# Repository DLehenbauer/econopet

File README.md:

# EconoPET

Open hardware mainboard replacement for Commodore PET/CBM 2001/30xx/40xx/80xx machines. The EconoPET can also run standalone with HDMI display and USB keyboard.

## User Resources

See the [project page](https://dlehenbauer.github.io/econopet) for user manual and firmware updates.

## Manufacturing

> **⚠️ Warning:** Rev A is not perfect. Before ordering, review the currently [known issues](https://github.com/DLehenbauer/econopet/issues?q=is%3Aissue%20label%3Arev-a%20label%3Aerrata) and understand that new issues may be discovered over time.

Rev. A has been released. For manufacturing and assembly instructions, go [here](https://dlehenbauer.github.io/econopet/manual/build-an-econopet/).

## Development

This project uses a [Dev Container](https://containers.dev/) for a consistent development environment on Windows, macOS, and Linux.

### Prerequisites

- [Docker](https://www.docker.com/)
- [VS Code](https://code.visualstudio.com/)
- [Dev Containers extension](https://marketplace.visualstudio.com/items?itemName=ms-vscode-remote.remote-containers)

### Workflow

This project uses [CMake](https://cmake.org/) to manage the build process for firmware, gateware, ROMs, and SD card package.

```sh
# Configure
cmake --preset default              # Do this first

# Build
cmake --build --preset all          # Build everything
cmake --build --preset boot         # Build the EconoPET SD-card bootloader
cmake --build --preset fw           # Build firmware only
cmake --build --preset fw-test      # Build firmware tests only
cmake --build --preset sys-test     # Build system integration tests
cmake --build --preset gw           # Build gateware only
cmake --build --preset rom          # Build ROMs only
cmake --build --preset sdcard       # Build SD card package

# Build and Program
cmake --build --preset prog-boot    # Build and program bootloader (over SWD)
cmake --build --preset prog-fw      # Build and program firmware (over SWD)
cmake --build --preset prog-gw      # Build and program gateware (over SWD)
cmake --build --preset prog         # Build and program bootloader, gateware, and firmware (over SWD)
cmake --build --preset reset        # Reset the MCU without reprogramming (over SWD)

# Test
ctest --preset all --parallel       # Run all tests
ctest --preset fw --parallel        # Run firmware tests only
ctest --preset sys                  # Run system integration suite only
ctest --preset gw --parallel        # Run gateware unit tests only
ctest --preset gw-boot --parallel   # Run full-boot benches (Verilator, minutes)
```

Gateware benches run under both simulators. `gw` runs both quick suites;
`gw-iv` and `gw-vl` run only Icarus or Verilator, respectively. Verilator is
two-state and settles differently, so it catches races Icarus tolerates. Each
suite takes under a minute. `ECONOPET_MEDIA_DIR` must point at the directory
containing `roms/` and `disks/`; `top_tb` and the boot bench load real ROMs
from its `roms/` subdirectory.

The [integration-test author guide](test/system/README.md) covers host, board
and firmware fixtures, checked CPU programs, ROM calls, and cooperative phases.
Use its nested CTest commands to filter individual integration cases or set
inner parallelism. The root `sys` preset selects the aggregate wrapper.

`gw-boot` is separate because it simulates seconds of PET time: it boots the
stock BASIC-4 ROMs on the soft 6502 and passes only once the banner, the RAM
sizing result and the `READY.` prompt are all on screen. That takes ~5 minutes
under Verilator and is impractical under Icarus. It prints the screen at the
end and writes `gw/EconoPET/outflow/stock6502_boot_tb.pgm`:

```
|*** COMMODORE BASIC 4.0 ***             |
|                                        |
| 31743 BYTES FREE                       |
|                                        |
|READY.                                  |
```

`ctest` hides that on success, so use `ctest --preset gw-boot --parallel -V` to see it, or
run `./verilate.sh stock6502_boot_tb 0` directly. See
[docs/dev/verilator.md](docs/dev/verilator.md) for the Verilator runner and
[docs/dev/testing.md](docs/dev/testing.md) for test seeding and replay.

## License

This project is released under the [CC0 1.0 Universal](LICENSE) (CC0) license, placing it in the public domain.

**Exception:** external dependencies are subject to their own licenses as noted in their respective source code and in [NOTICE.md](NOTICE.md).

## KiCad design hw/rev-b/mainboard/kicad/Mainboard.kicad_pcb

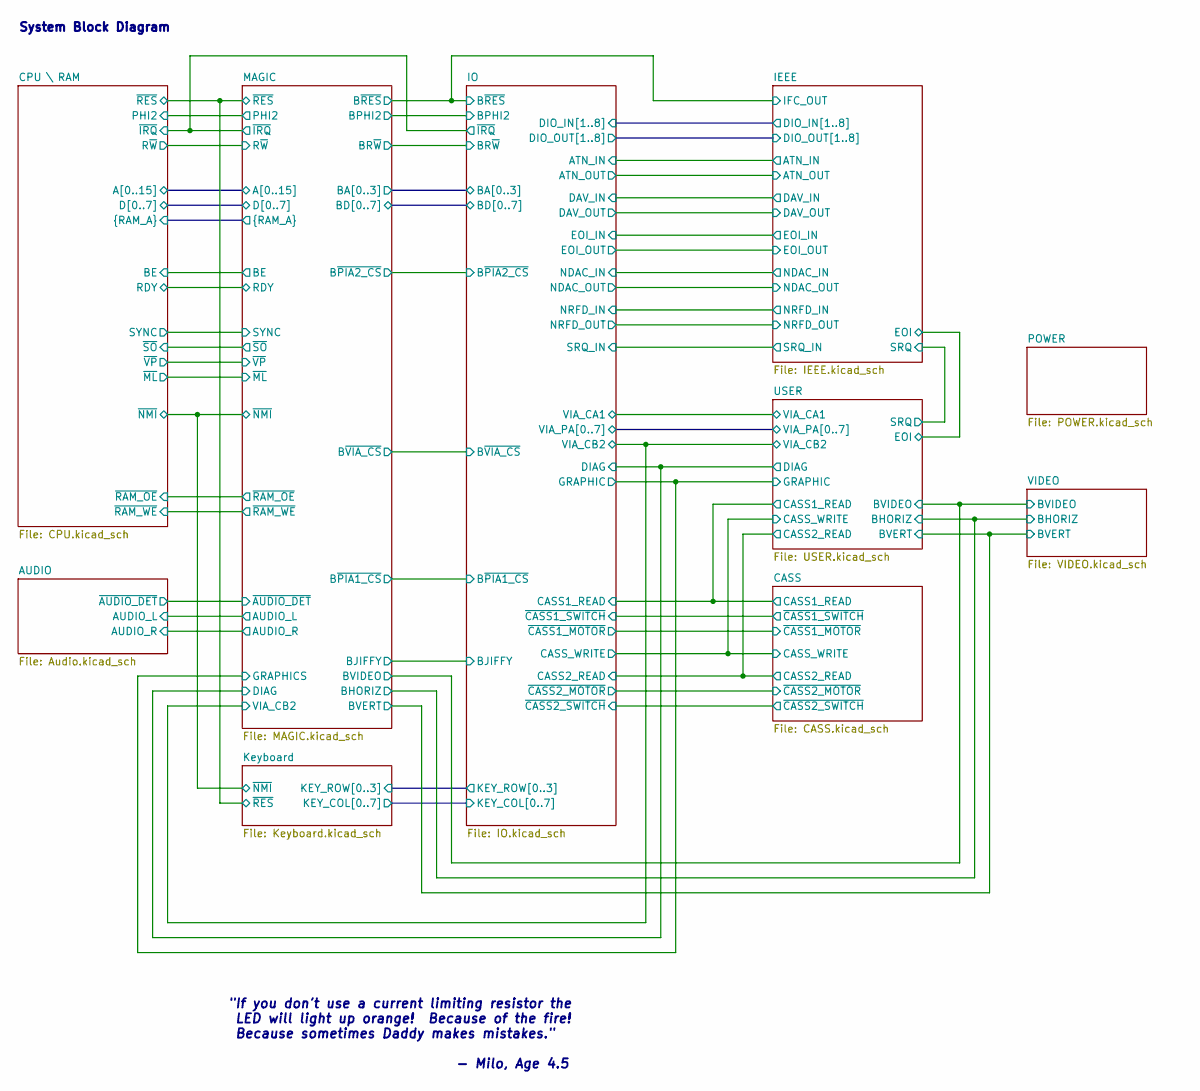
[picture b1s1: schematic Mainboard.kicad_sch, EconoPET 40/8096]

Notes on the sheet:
"If you don't use a current limiting resistor the LED will light up orange! Because of the fire! Because sometimes Daddy makes mistakes." - Milo, Age 4.5
System Block Diagram

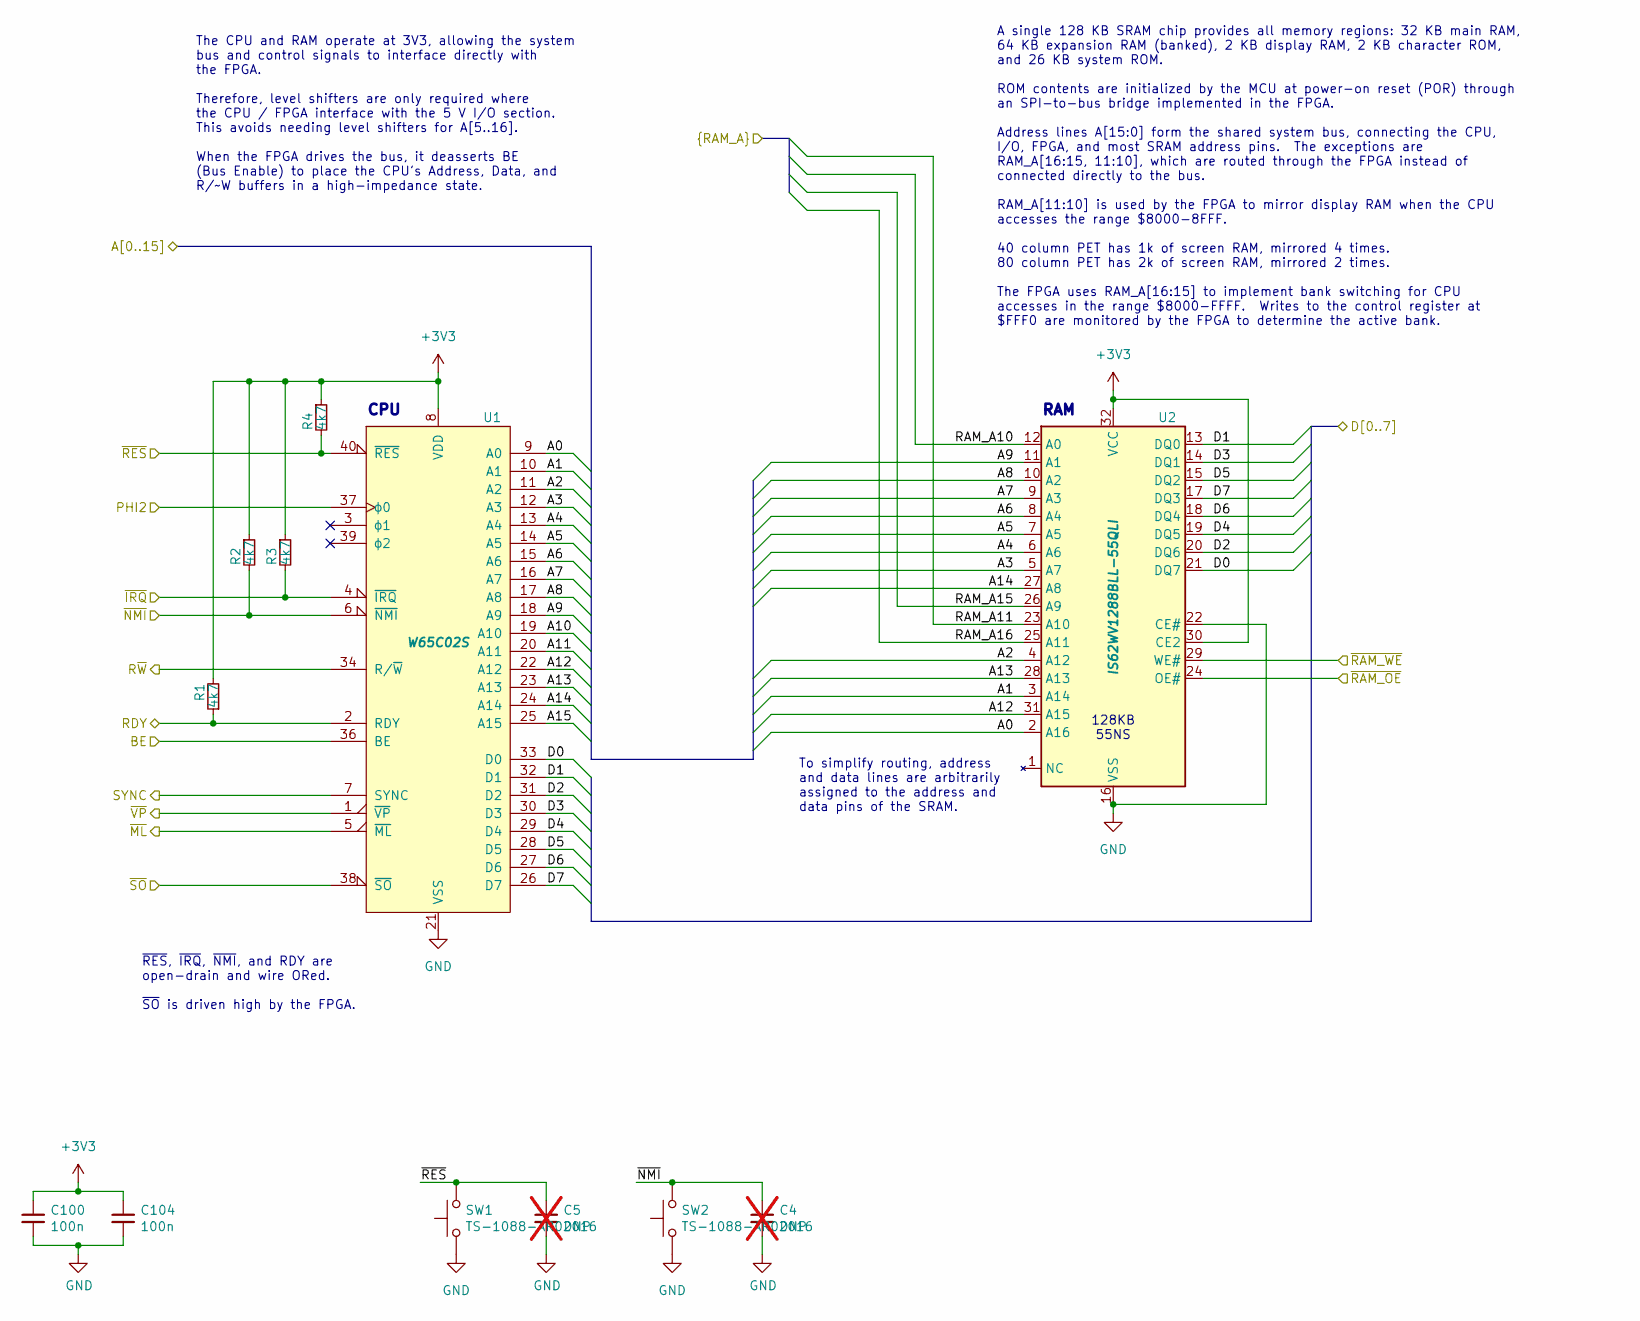
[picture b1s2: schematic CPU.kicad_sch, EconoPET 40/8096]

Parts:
C4, C5: DNP; C_0402_1005Metric; not fitted
C100, C104: 100n; C_0402_1005Metric; LCSC Part # C307331
R1, R2, R3, R4: 4k7; R_0402_1005Metric; LCSC Part # C25900
SW1, SW2: TS-1088-AR02016; SW-SMD_L3.9-W3.0-P4.45; LCSC Part # C720477
U1: W65C02S; DIP-40_W15.24mm_Socket; MOUSER 955-W65C02S6TPG-14,571-1-2199299-5
U2: IS62WV1288BLL-55QLI; SOP-32_L20.7-W11.3-P1.27-LS14.1-BL; LCSC Part # C1351025

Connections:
+3V3: C100.1, C104.1, R1.2, R2.1, R3.1, R4.1, U1.8 (VDD), U2.30 (CE2), U2.32 (VCC); also elsewhere on the board
/CPU \ RAM/A0: U1.9 (A0), U2.2 (A16); also elsewhere on the board
/CPU \ RAM/A1: U1.10 (A1), U2.3 (A14); also elsewhere on the board
/CPU \ RAM/A2: U1.11 (A2), U2.4 (A12); also elsewhere on the board
/CPU \ RAM/A3: U1.12 (A3), U2.5 (A7); also elsewhere on the board
/CPU \ RAM/A4: U1.13 (A4), U2.6 (A6); also elsewhere on the board
/CPU \ RAM/A5: U1.14 (A5), U2.7 (A5); also elsewhere on the board
/CPU \ RAM/A6: U1.15 (A6), U2.8 (A4); also elsewhere on the board
/CPU \ RAM/A7: U1.16 (A7), U2.9 (A3); also elsewhere on the board
/CPU \ RAM/A8: U1.17 (A8), U2.10 (A2); also elsewhere on the board
/CPU \ RAM/A9: U1.18 (A9), U2.11 (A1); also elsewhere on the board
/CPU \ RAM/A10: U1.19 (A10); also elsewhere on the board
/CPU \ RAM/A11: U1.20 (A11); also elsewhere on the board
/CPU \ RAM/A12: U1.22 (A12), U2.31 (A15); also elsewhere on the board
/CPU \ RAM/A13: U1.23 (A13), U2.28 (A13); also elsewhere on the board
/CPU \ RAM/A14: U1.24 (A14), U2.27 (A8); also elsewhere on the board
/CPU \ RAM/A15: U1.25 (A15); also elsewhere on the board
/CPU \ RAM/D0: U1.33 (D0), U2.21 (DQ7); also elsewhere on the board
/CPU \ RAM/D1: U1.32 (D1), U2.13 (DQ0); also elsewhere on the board
/CPU \ RAM/D2: U1.31 (D2), U2.20 (DQ6); also elsewhere on the board
/CPU \ RAM/D3: U1.30 (D3), U2.14 (DQ1); also elsewhere on the board
/CPU \ RAM/D4: U1.29 (D4), U2.19 (DQ5); also elsewhere on the board
/CPU \ RAM/D5: U1.28 (D5), U2.15 (DQ2); also elsewhere on the board
/CPU \ RAM/D6: U1.27 (D6), U2.18 (DQ4); also elsewhere on the board
/CPU \ RAM/D7: U1.26 (D7), U2.17 (DQ3); also elsewhere on the board
/CPU \ RAM/RAM_A10: U2.12 (A0); also elsewhere on the board
/CPU \ RAM/RAM_A11: U2.23 (A10); also elsewhere on the board
/CPU \ RAM/RAM_A15: U2.26 (A9); also elsewhere on the board
/CPU \ RAM/RAM_A16: U2.25 (A11); also elsewhere on the board
/CPU \ RAM/~ML: U1.5 (~ML); also elsewhere on the board
/CPU \ RAM/~NMI: C4.1, R2.2, SW2.2, U1.6 (~NMI); also elsewhere on the board
/CPU \ RAM/~RAM_OE: U2.24 (OE#); also elsewhere on the board
/CPU \ RAM/~RAM_WE: U2.29 (WE#); also elsewhere on the board
/CPU \ RAM/~RES: C5.1, R4.2, SW1.2, U1.40 (~RES); also elsewhere on the board
/CPU \ RAM/~VP: U1.1 (~VP); also elsewhere on the board
/MAGIC/FPGA/BE: U1.36 (BE); also elsewhere on the board
/MAGIC/FPGA/RDY: R1.1, U1.2 (RDY); also elsewhere on the board
/MAGIC/FPGA/SYNC: U1.7 (SYNC); also elsewhere on the board
/MAGIC/FPGA/~IRQ: R3.2, U1.4 (~IRQ); also elsewhere on the board
/MAGIC/FPGA/~SO: U1.38 (~SO); also elsewhere on the board
/MAGIC/PHI2: U1.37 (ϕ0); also elsewhere on the board
/MAGIC/R~W: U1.34 (R/~W); also elsewhere on the board
GND: C4.2, C5.2, C100.2, C104.2, SW1.1, SW2.1, U1.21 (VSS), U2.16 (VSS), U2.22 (CE#); also elsewhere on the board

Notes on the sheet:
RAM
A single 128 KB SRAM chip provides all memory regions: 32 KB main RAM, 64 KB expansion RAM (banked), 2 KB display RAM, 2 KB character ROM, and 26 KB system ROM. ROM contents are initialized by the MCU at power-on reset (POR) through an SPI-to-bus bridge implemented in the FPGA. Address lines A[15:0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
To simplify routing, address and data lines are arbitrarily assigned to the address and data pins of the SRAM.
~{RES}, ~{IRQ}, ~{NMI}, and RDY are open-drain and wire ORed. ~{SO} is driven high by the FPGA.
128KB 55NS
CPU
The CPU and RAM operate at 3V3, allowing the system bus and control signals to interface directly with the FPGA. Therefore, level shifters are only required where the CPU / FPGA interface with the 5 V I/O section. This avoids needing level shifters for A[5..16]. When the FPGA drives the bus, it dea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

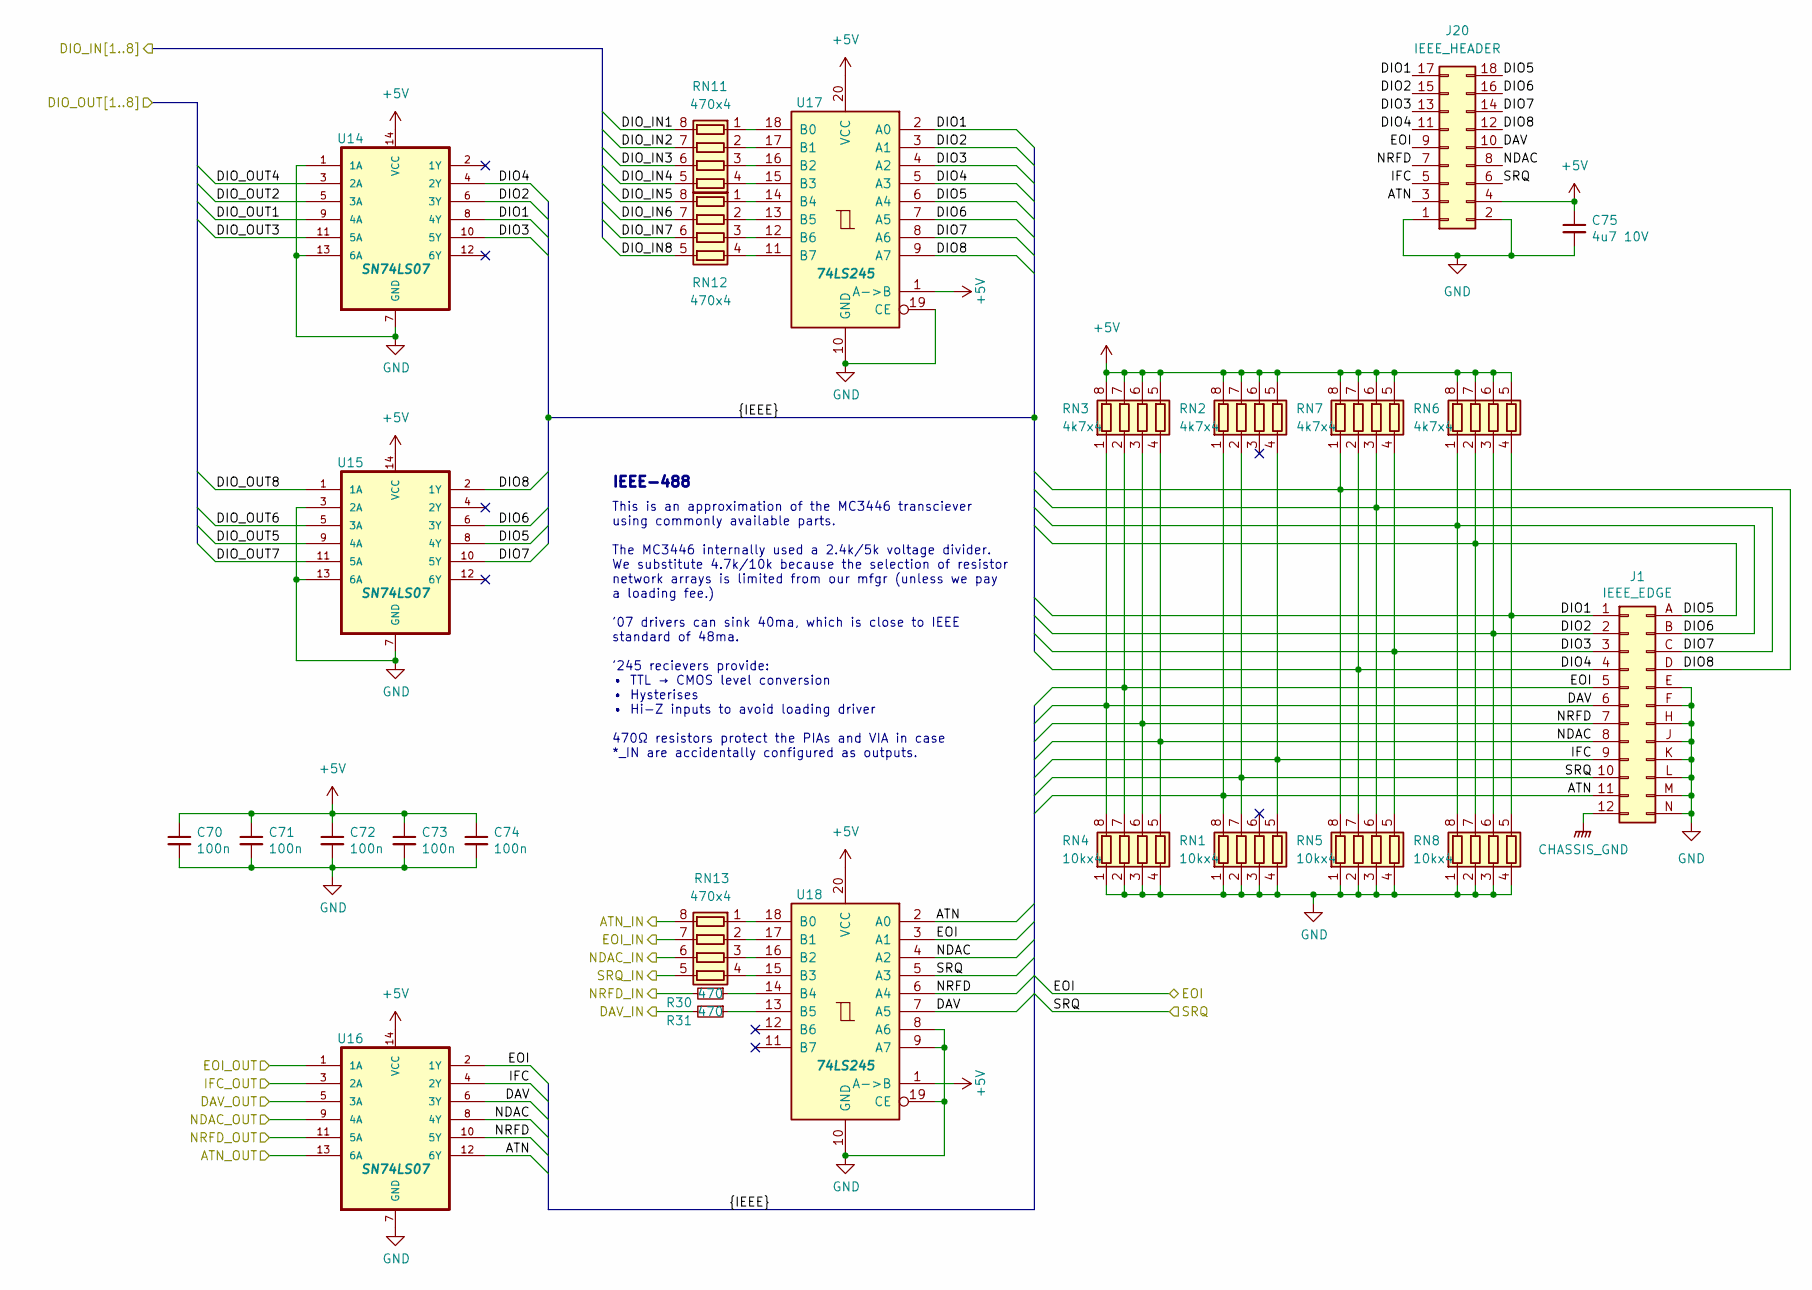
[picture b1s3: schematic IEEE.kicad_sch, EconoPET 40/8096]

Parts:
C70, C71, C72, C73, C74: 100n; C_0402_1005Metric; LCSC Part # C307331
C75: 4u7 10V; C_0402_1005Metric; LCSC Part # C23733
J1: IEEE_EDGE; CBM_PET_IEEE_EDGE_CON_24P
J20: IEEE_HEADER; PinHeader_2x09_P2.54mm_Vertical; MOUSER 649-1012938195002BLF
R30, R31: 470; R_0402_1005Metric; LCSC Part # C25117
RN1, RN4, RN5, RN8: 10kx4; R_Array_Convex_4x0603; LCSC Part # C29718
RN2, RN3, RN6, RN7: 4k7x4; R_Array_Convex_4x0603; LCSC Part # C1980
RN11, RN12, RN13: 470x4; R_Array_Convex_4x0603; LCSC Part # C25510
U14, U15, U16: SN74LS07; SOIC-14_3.9x8.7mm_P1.27mm; LCSC Part # C513513
U17, U18: 74LS245; SOIC-20W_7.5x12.8mm_P1.27mm; LCSC Part # C129580

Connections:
+5V: C70.1, C71.1, C72.1, C73.1, C74.1, C75.1, J20.4, RN2.5 (R4.2), RN2.6 (R3.2), RN2.7 (R2.2), RN2.8 (R1.2), RN3.5 (R4.2), RN3.6 (R3.2), RN3.7 (R2.2), RN3.8 (R1.2), RN6.5 (R4.2), RN6.6 (R3.2), RN6.7 (R2.2), RN6.8 (R1.2), RN7.5 (R4.2), RN7.6 (R3.2), RN7.7 (R2.2), RN7.8 (R1.2), U14.14 (VCC), U15.14 (VCC), U16.14 (VCC), U17.1 (A->B), U17.20 (VCC), U18.1 (A->B), U18.20 (VCC); also elsewhere on the board
/IEEE/ATN: J1.11 (ATN), J20.3, RN1.8 (R1.2), RN2.1 (R1.1), U16.12 (6Y), U18.2 (A0)
/IEEE/ATN_IN: RN13.8 (R1.2); also elsewhere on the board
/IEEE/ATN_OUT: U16.13 (6A); also elsewhere on the board
/IEEE/DAV: J1.6 (DAV), J20.10, RN3.1 (R1.1), RN4.8 (R1.2), U16.6 (3Y), U18.7 (A5)
/IEEE/DAV_IN: R31.2; also elsewhere on the board
/IEEE/DAV_OUT: U16.5 (3A); also elsewhere on the board
/IEEE/DIO1: J1.1 (DIO1), J20.17, RN6.4 (R4.1), RN8.5 (R4.2), U14.8 (4Y), U17.2 (A0)
/IEEE/DIO2: J1.2 (DIO2), J20.15, RN6.3 (R3.1), RN8.6 (R3.2), U14.6 (3Y), U17.3 (A1)
/IEEE/DIO3: J1.3 (DIO3), J20.13, RN5.5 (R4.2), RN7.4 (R4.1), U14.10 (5Y), U17.4 (A2)
/IEEE/DIO4: J1.4 (DIO4), J20.11, RN5.7 (R2.2), RN7.2 (R2.1), U14.4 (2Y), U17.5 (A3)
/IEEE/DIO5: J1.A (DIO5), J20.18, RN6.2 (R2.1), RN8.7 (R2.2), U15.8 (4Y), U17.6 (A4)
/IEEE/DIO6: J1.B (DIO6), J20.16, RN6.1 (R1.1), RN8.8 (R1.2), U15.6 (3Y), U17.7 (A5)
/IEEE/DIO7: J1.C (DIO7), J20.14, RN5.6 (R3.2), RN7.3 (R3.1), U15.10 (5Y), U17.8 (A6)
/IEEE/DIO8: J1.D (DIO8), J20.12, RN5.8 (R1.2), RN7.1 (R1.1), U15.2 (1Y), U17.9 (A7)
/IEEE/DIO_IN1: RN11.8 (R1.2); also elsewhere on the board
/IEEE/DIO_IN2: RN11.7 (R2.2); also elsewhere on the board
/IEEE/DIO_IN3: RN11.6 (R3.2); also elsewhere on the board
/IEEE/DIO_IN4: RN11.5 (R4.2); also elsewhere on the board
/IEEE/DIO_IN5: RN12.8 (R1.2); also elsewhere on the board
/IEEE/DIO_IN6: RN12.7 (R2.2); also elsewhere on the board
/IEEE/DIO_IN7: RN12.6 (R3.2); also elsewhere on the board
/IEEE/DIO_IN8: RN12.5 (R4.2); also elsewhere on the board
/IEEE/DIO_OUT1: U14.9 (4A); also elsewhere on the board
/IEEE/DIO_OUT2: U14.5 (3A); also elsewhere on the board
/IEEE/DIO_OUT3: U14.11 (5A); also elsewhere on the board
/IEEE/DIO_OUT4: U14.3 (2A); also elsewhere on the board
/IEEE/DIO_OUT5: U15.9 (4A); also elsewhere on the board
/IEEE/DIO_OUT6: U15.5 (3A); also elsewhere on the board
/IEEE/DIO_OUT7: U15.11 (5A); also elsewhere on the board
/IEEE/DIO_OUT8: U15.1 (1A); also elsewhere on the board
/IEEE/EOI: J1.5 (EOI), J20.9, RN3.2 (R2.1), RN4.7 (R2.2), U16.2 (1Y), U18.3 (A1); also elsewhere on the board
/IEEE/EOI_IN: RN13.7 (R2.2); also elsewhere on the board
/IEEE/EOI_OUT: U16.1 (1A); also elsewhere on the board
/IEEE/IFC: J1.9 (IFC), J20.5, RN1.5 (R4.2), RN2.4 (R4.1), U16.4 (2Y)
/IEEE/IFC_OUT: U16.3 (2A); also elsewhere on the board
/IEEE/NDAC: J1.8 (NDAC), J20.8, RN3.4 (R4.1), RN4.5 (R4.2), U16.8 (4Y), U18.4 (A2)
/IEEE/NDAC_IN: RN13.6 (R3.2); also elsewhere on the board
/IEEE/NDAC_OUT: U16.9 (4A); also elsewhere on the board
/IEEE/NRFD: J1.7 (NRFD), J20.7, RN3.3 (R3.1), RN4.6 (R3.2), U16.10 (5Y), U18.6 (A4)
/IEEE/NRFD_IN: R30.2; also elsewhere on the board
/IEEE/NRFD_OUT: U16.11 (5A); also elsewhere on the board
/IEEE/SRQ: J1.10 (SRQ), J20.6, RN1.7 (R2.2), RN2.2 (R2.1), U18.5 (A3); also elsewhere on the board
/IEEE/SRQ_IN: RN13.5 (R4.2); also elsewhere on the board
CHASSIS_GND: J1.12 (GND); also elsewhere on the board
GND: C70.2, C71.2, C72.2, C73.2, C74.2, C75.2, J1.E (GND), J1.F (GND), J1.H (GND), J1.J (GND), J1.K (GND), J1.L (GND), J1.M (GND), J1.N (GND), J20.1, J20.2, RN1.1 (R1.1), RN1.2 (R2.1), RN1.3 (R3.1), RN1.4 (R4.1), RN4.1 (R1.1), RN4.2 (R2.1), RN4.3 (R3.1), RN4.4 (R4.1), RN5.1 (R1.1), RN5.2 (R2.1), RN5.3 (R3.1), RN5.4 (R4.1), RN8.1 (R1.1), RN8.2 (R2.1), RN8.3 (R3.1), RN8.4 (R4.1), U14.1 (1A), U14.7 (GND), U14.13 (6A), U15.3 (2A), U15.7 (GND), U15.13 (6A), U16.7 (GND), U17.10 (GND), U17.19 (CE), U18.8 (A6), U18.9 (A7), U18.10 (GND), U18.19 (CE); also elsewhere on the board
unnamed: RN11.1 (R1.1), U17.18 (B0)
unnamed: RN11.2 (R2.1), U17.17 (B1)
unnamed: RN11.3 (R3.1), U17.16 (B2)
unnamed: RN11.4 (R4.1), U17.15 (B3)
unnamed: RN12.1 (R1.1), U17.14 (B4)
unnamed: RN12.2 (R2.1), U17.13 (B5)
unnamed: RN12.3 (R3.1), U17.12 (B6)
unnamed: RN12.4 (R4.1), U17.11 (B7)
unnamed: RN13.1 (R1.1), U18.18 (B0)
unnamed: RN13.2 (R2.1), U18.17 (B1)
unnamed: RN13.3 (R3.1), U18.16 (B2)
unnamed: RN13.4 (R4.1), U18.15 (B3)
unnamed: R30.1, U18.14 (B4)
unnamed: R31.1, U18.13 (B5)

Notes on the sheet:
This is an approximation of the MC3446 transciever using commonly available parts. The MC3446 internally used a 2.4k/5k voltage divider. We substitute 4.7k/10k because the selection of resistor network arrays is limited from our mfgr (unless we pay a loading fee.) '07 drivers can sink 40ma, which i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
IEEE-488

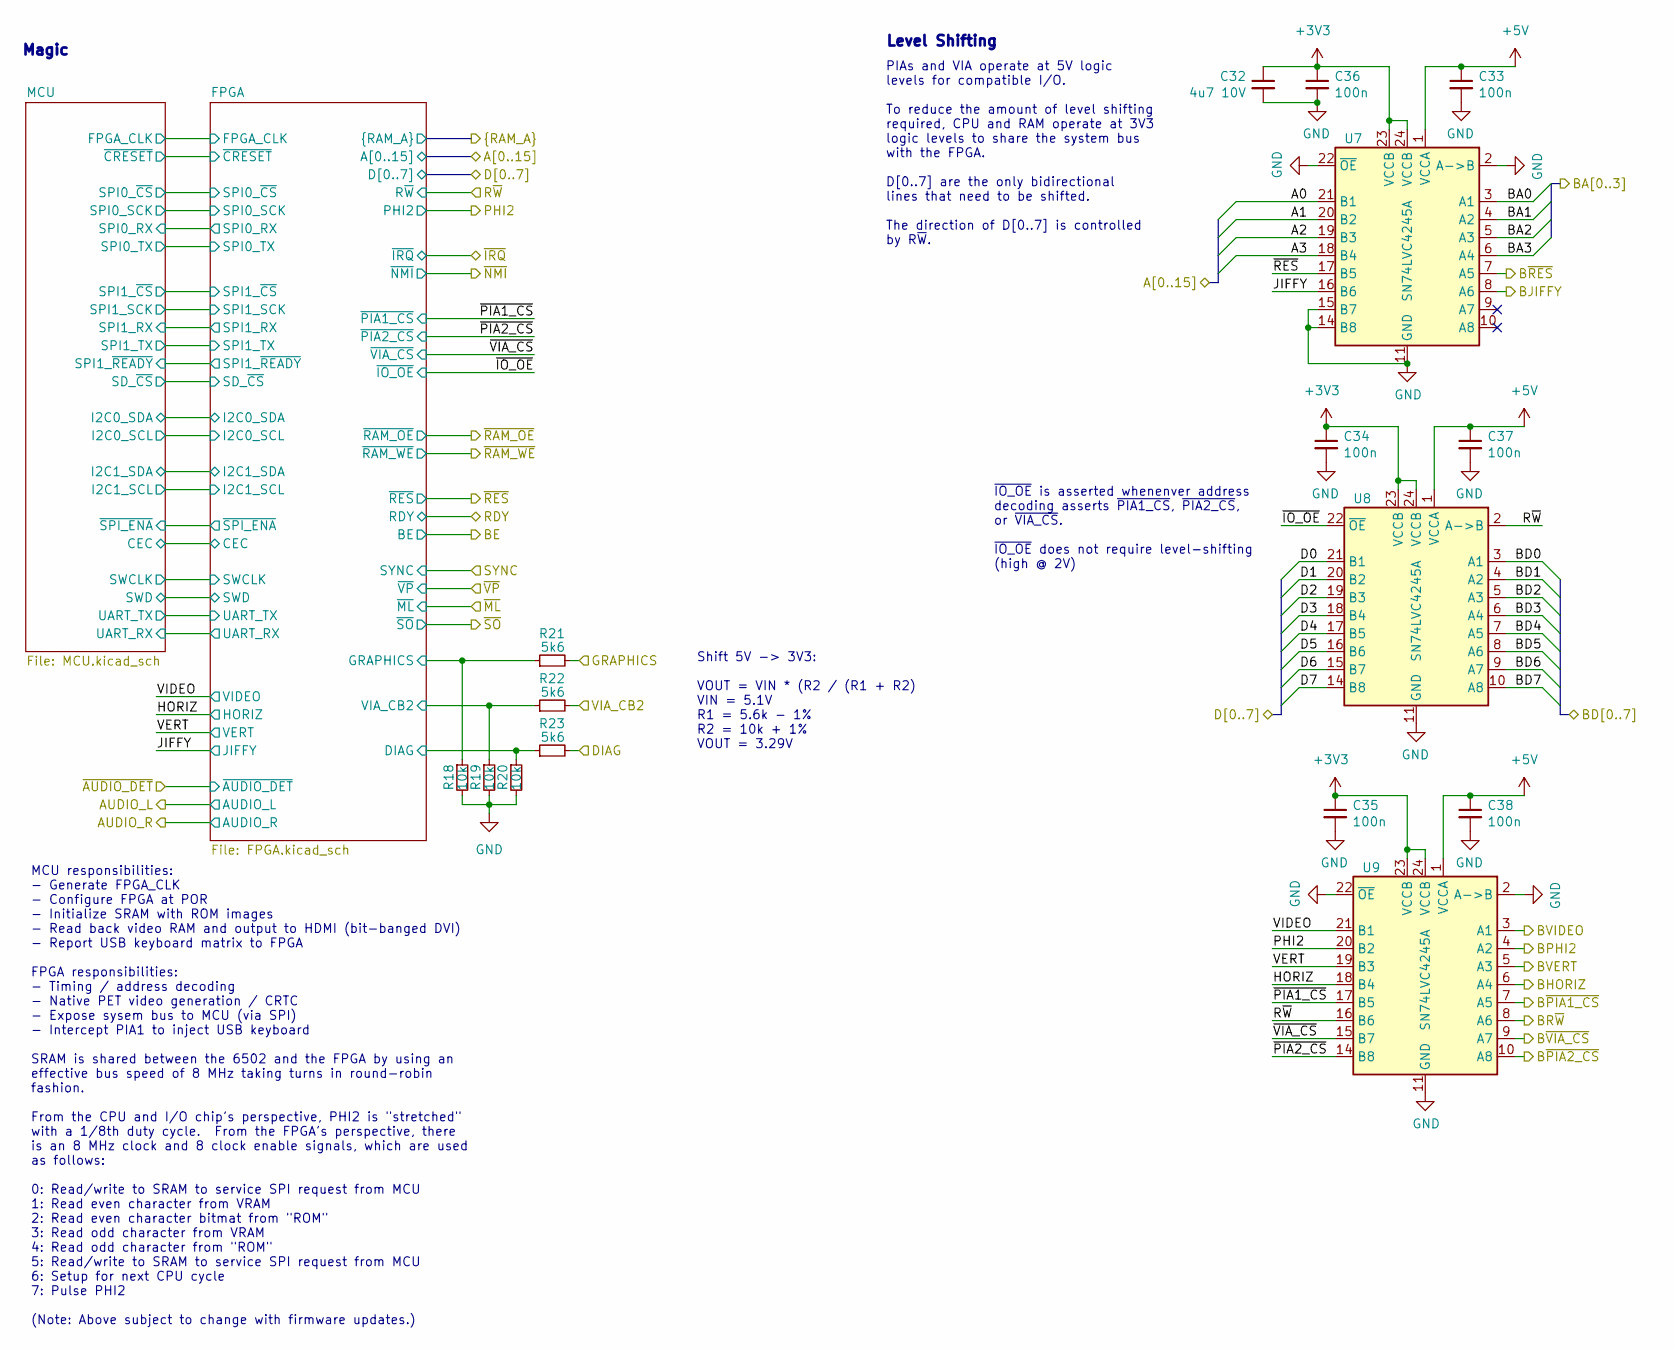
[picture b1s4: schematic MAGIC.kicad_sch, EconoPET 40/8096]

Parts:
C32: 4u7 10V; C_0402_1005Metric; LCSC Part # C23733
C33, C34, C35, C36, C37, C38: 100n; C_0402_1005Metric; LCSC Part # C307331
R18, R19, R20: 10k; R_0402_1005Metric; LCSC Part # C25744
R21, R22, R23: 5k6; R_0402_1005Metric; LCSC Part # C25908
U7, U8, U9: SN74LVC4245A; TSSOP-24_4.4x7.8mm_P0.65mm; LCSC Part # C7859

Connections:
+3V3: C32.1, C34.1, C35.1, C36.1, U7.23 (VCCB), U7.24 (VCCB), U8.23 (VCCB), U8.24 (VCCB), U9.23 (VCCB), U9.24 (VCCB); also elsewhere on the board
+5V: C33.1, C37.1, C38.1, U7.1 (VCCA), U8.1 (VCCA), U9.1 (VCCA); also elsewhere on the board
/CPU \ RAM/A0: U7.21 (B1); also elsewhere on the board
/CPU \ RAM/A1: U7.20 (B2); also elsewhere on the board
/CPU \ RAM/A2: U7.19 (B3); also elsewhere on the board
/CPU \ RAM/A3: U7.18 (B4); also elsewhere on the board
/CPU \ RAM/D0: U8.21 (B1); also elsewhere on the board
/CPU \ RAM/D1: U8.20 (B2); also elsewhere on the board
/CPU \ RAM/D2: U8.19 (B3); also elsewhere on the board
/CPU \ RAM/D3: U8.18 (B4); also elsewhere on the board
/CPU \ RAM/D4: U8.17 (B5); also elsewhere on the board
/CPU \ RAM/D5: U8.16 (B6); also elsewhere on the board
/CPU \ RAM/D6: U8.15 (B7); also elsewhere on the board
/CPU \ RAM/D7: U8.14 (B8); also elsewhere on the board
/CPU \ RAM/~RES: U7.17 (B5); also elsewhere on the board
/IEEE/IFC_OUT: U7.7 (A5); also elsewhere on the board
/IO/BA0: U7.3 (A1); also elsewhere on the board
/IO/BA1: U7.4 (A2); also elsewhere on the board
/IO/BA2: U7.5 (A3); also elsewhere on the board
/IO/BA3: U7.6 (A4); also elsewhere on the board
/IO/BD0: U8.3 (A1); also elsewhere on the board
/IO/BD1: U8.4 (A2); also elsewhere on the board
/IO/BD2: U8.5 (A3); also elsewhere on the board
/IO/BD3: U8.6 (A4); also elsewhere on the board
/IO/BD4: U8.7 (A5); also elsewhere on the board
/IO/BD5: U8.8 (A6); also elsewhere on the board
/IO/BD6: U8.9 (A7); also elsewhere on the board
/IO/BD7: U8.10 (A8); also elsewhere on the board
/IO/BJIFFY: U7.8 (A6); also elsewhere on the board
/IO/BPHI2: U9.4 (A2); also elsewhere on the board
/IO/BR~W: U9.8 (A6); also elsewhere on the board
/IO/B~PIA1_CS: U9.7 (A5); also elsewhere on the board
/IO/B~PIA2_CS: U9.10 (A8); also elsewhere on the board
/IO/B~VIA_CS: U9.9 (A7); also elsewhere on the board
/IO/DIAG: R23.2; also elsewhere on the board
/IO/GRAPHIC: R21.2; also elsewhere on the board
/IO/VIA_CB2: R22.2; also elsewhere on the board
/MAGIC/BHORIZ: U9.6 (A4); also elsewhere on the board
/MAGIC/BVERT: U9.5 (A3); also elsewhere on the board
/MAGIC/BVIDEO: U9.3 (A1); also elsewhere on the board
/MAGIC/FPGA/DIAG: R20.1, R23.1; also elsewhere on the board
/MAGIC/FPGA/GRAPHICS: R18.1, R21.1; also elsewhere on the board
/MAGIC/FPGA/VIA_CB2: R19.1, R22.1; also elsewhere on the board
/MAGIC/HORIZ: U9.18 (B4); also elsewhere on the board
/MAGIC/JIFFY: U7.16 (B6); also elsewhere on the board
/MAGIC/PHI2: U9.20 (B2); also elsewhere on the board
/MAGIC/R~W: U8.2 (A->B), U9.16 (B6); also elsewhere on the board
/MAGIC/VERT: U9.19 (B3); also elsewhere on the board
/MAGIC/VIDEO: U9.21 (B1); also elsewhere on the board
/MAGIC/~IO_OE: U8.22 (~OE); also elsewhere on the board
/MAGIC/~PIA1_CS: U9.17 (B5); also elsewhere on the board
/MAGIC/~PIA2_CS: U9.14 (B8); also elsewhere on the board
/MAGIC/~VIA_CS: U9.15 (B7); also elsewhere on the board
GND: C32.2, C33.2, C34.2, C35.2, C36.2, C37.2, C38.2, R18.2, R19.2, R20.2, U7.2 (A->B), U7.11 (GND), U7.12 (GND), U7.13 (GND), U7.14 (B8), U7.15 (B7), U7.22 (~OE), U8.11 (GND), U8.12 (GND), U8.13 (GND), U9.2 (A->B), U9.11 (GND), U9.12 (GND), U9.13 (GND), U9.22 (~OE); also elsewhere on the board

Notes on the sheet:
PIAs and VIA operate at 5V logic levels for compatible I/O. To reduce the amount of level shifting required, CPU and RAM operate at 3V3 logic levels to share the system bus with the FPGA. D[0..7] are the only bidirectional lines that need to be shifted. The direction of D[0..7] is controlled by R~{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
Level Shifting
Magic
MCU responsibilities: - Generate FPGA_CLK - Configure FPGA at POR - Initialize SRAM with ROM images - Read back video RAM and output to HDMI (bit-banged DVI) - Report USB keyboard matrix to FPGA FPGA responsibilities: - Timing / address decoding - Native PET video generation / CRTC - Expose sysem b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
~{IO_OE} is asserted whenenver address decoding asserts ~{PIA1_CS}, ~{PIA2_CS}, or ~{VIA_CS}. ~{IO_OE} does not require level-shifting (high @ 2V)
Shift 5V -> 3V3: VOUT = VIN * (R2 / (R1 + R2) VIN = 5.1V R1 = 5.6k - 1% R2 = 10k + 1% VOUT = 3.29V

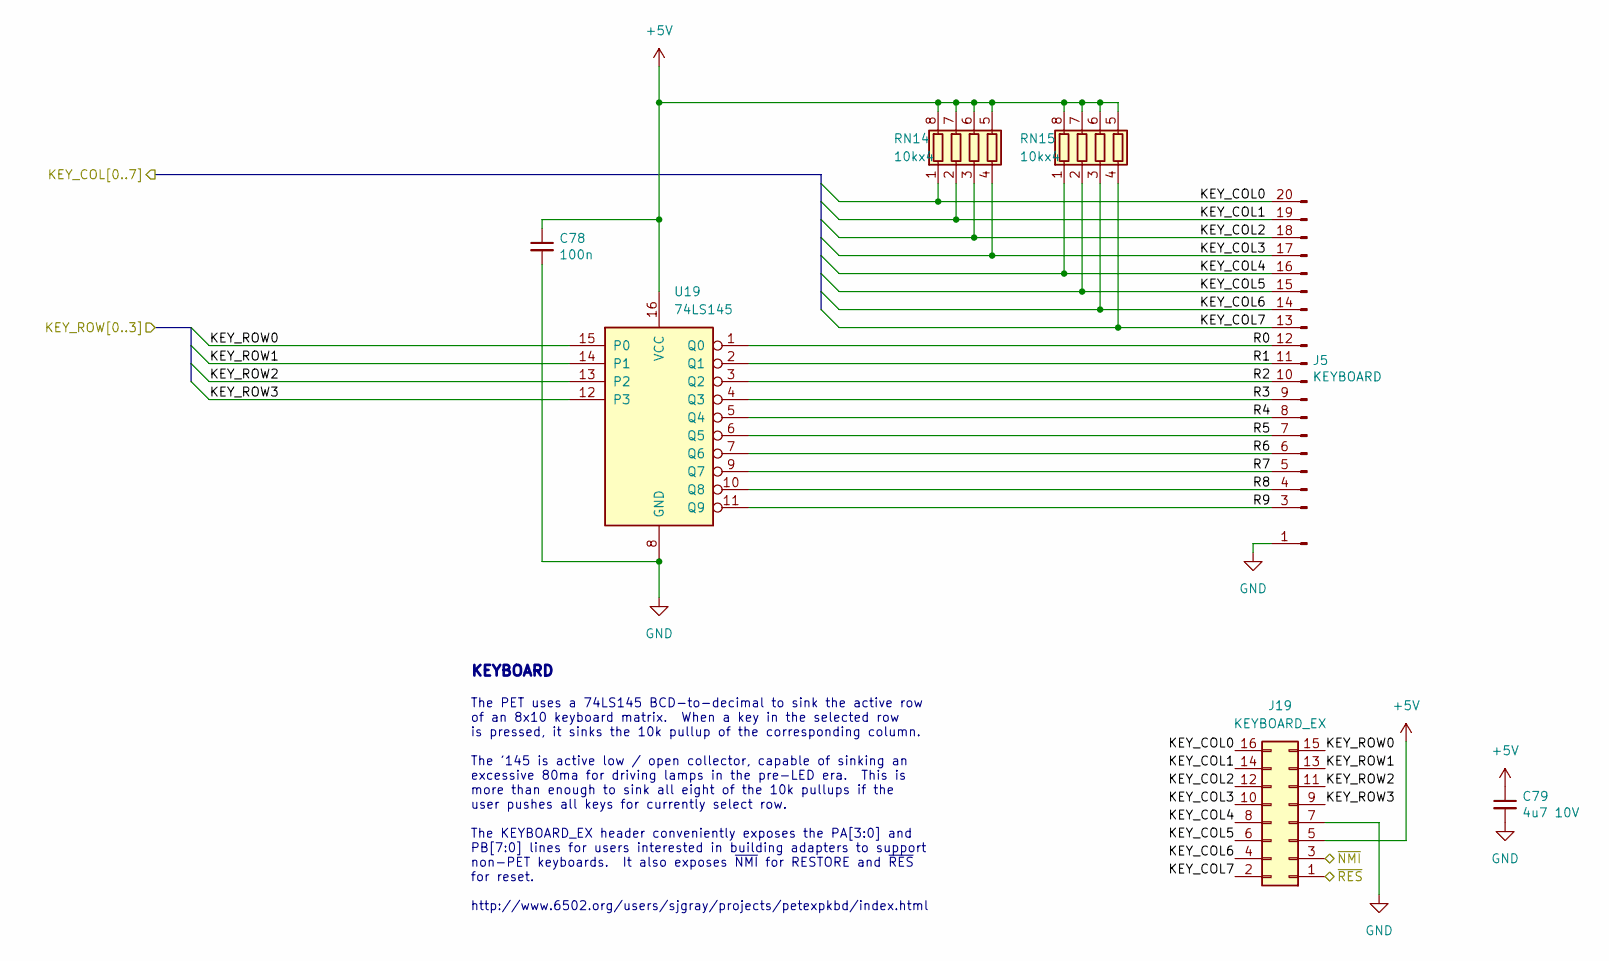
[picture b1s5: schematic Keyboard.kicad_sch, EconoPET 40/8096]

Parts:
C78: 100n; C_0402_1005Metric; LCSC Part # C307331
C79: 4u7 10V; C_0402_1005Metric; LCSC Part # C23733
J5: KEYBOARD; CBM_PET_KEYBOARD_KEYED_20P; MOUSER 649-1012937893603BLF
J19: KEYBOARD_EX; PinHeader_2x08_P2.54mm_Vertical; MOUSER 649-1012938195002BLF
RN14, RN15: 10kx4; R_Array_Convex_4x0603; LCSC Part # C29718
U19: 74LS145; SOIC-16_3.9x9.9mm_P1.27mm; LCSC Part # C60829

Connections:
+5V: C78.1, C79.1, J19.5, RN14.5 (R4.2), RN14.6 (R3.2), RN14.7 (R2.2), RN14.8 (R1.2), RN15.5 (R4.2), RN15.6 (R3.2), RN15.7 (R2.2), RN15.8 (R1.2), U19.16 (VCC); also elsewhere on the board
/CPU \ RAM/~NMI: J19.3; also elsewhere on the board
/CPU \ RAM/~RES: J19.1; also elsewhere on the board
/IO/KEY_COL0: J5.20, J19.16, RN14.1 (R1.1); also elsewhere on the board
/IO/KEY_COL1: J5.19, J19.14, RN14.2 (R2.1); also elsewhere on the board
/IO/KEY_COL2: J5.18, J19.12, RN14.3 (R3.1); also elsewhere on the board
/IO/KEY_COL3: J5.17, J19.10, RN14.4 (R4.1); also elsewhere on the board
/IO/KEY_COL4: J5.16, J19.8, RN15.1 (R1.1); also elsewhere on the board
/IO/KEY_COL5: J5.15, J19.6, RN15.2 (R2.1); also elsewhere on the board
/IO/KEY_COL6: J5.14, J19.4, RN15.3 (R3.1); also elsewhere on the board
/IO/KEY_COL7: J5.13, J19.2, RN15.4 (R4.1); also elsewhere on the board
/IO/KEY_ROW0: J19.15, U19.15 (P0); also elsewhere on the board
/IO/KEY_ROW1: J19.13, U19.14 (P1); also elsewhere on the board
/IO/KEY_ROW2: J19.11, U19.13 (P2); also elsewhere on the board
/IO/KEY_ROW3: J19.9, U19.12 (P3); also elsewhere on the board
/Keyboard/R0: J5.12, U19.1 (Q0)
/Keyboard/R1: J5.11, U19.2 (Q1)
/Keyboard/R2: J5.10, U19.3 (Q2)
/Keyboard/R3: J5.9, U19.4 (Q3)
/Keyboard/R4: J5.8, U19.5 (Q4)
/Keyboard/R5: J5.7, U19.6 (Q5)
/Keyboard/R6: J5.6, U19.7 (Q6)
/Keyboard/R7: J5.5, U19.9 (Q7)
/Keyboard/R8: J5.4, U19.10 (Q8)
/Keyboard/R9: J5.3, U19.11 (Q9)
GND: C78.2, C79.2, J5.1, J19.7, U19.8 (GND); also elsewhere on the board

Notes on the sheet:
The PET uses a 74LS145 BCD-to-decimal to sink the active row of an 8x10 keyboard matrix. When a key in the selected row is pressed, it sinks the 10k pullup of the corresponding column. The '145 is active low / open collector, capable of sinking an excessive 80ma for driving lamps in the pre-LED era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
KEYBOARD

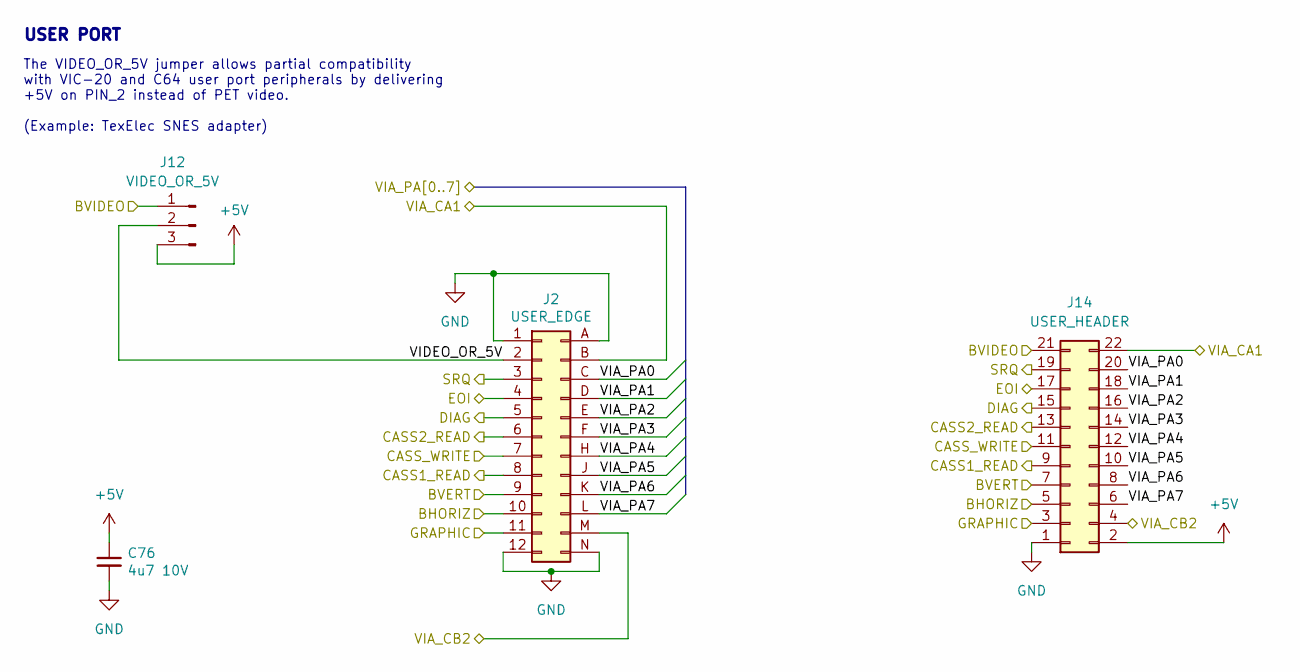
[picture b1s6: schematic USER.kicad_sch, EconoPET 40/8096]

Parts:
C76: 4u7 10V; C_0402_1005Metric; LCSC Part # C23733
J2: USER_EDGE; CBM_PET_USER_EDGE_CON_24P
J12: VIDEO_OR_5V; PinHeader_1x03_P2.54mm_Vertical_or_SolderJumper
J14: USER_HEADER; PinHeader_2x11_P2.54mm_Vertical; MOUSER 649-1012938195002BLF

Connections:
+5V: C76.1, J12.3, J14.2; also elsewhere on the board
/CASS/CASS1_READ: J2.8 (CASS1_READ), J14.9; also elsewhere on the board
/CASS/CASS2_READ: J2.6 (CASS2_READ), J14.13; also elsewhere on the board
/CASS/CASS_WRITE: J2.7 (CASS_WRITE), J14.11; also elsewhere on the board
/IEEE/EOI: J2.4 (EOI), J14.17; also elsewhere on the board
/IEEE/SRQ: J2.3 (SRQ), J14.19; also elsewhere on the board
/IO/DIAG: J2.5 (DIAG), J14.15; also elsewhere on the board
/IO/GRAPHIC: J2.11 (GRAPHIC), J14.3; also elsewhere on the board
/IO/VIA_CA1: J2.B (VIA_CA1), J14.22; also elsewhere on the board
/IO/VIA_CB2: J2.M (VIA_CB2), J14.4; also elsewhere on the board
/IO/VIA_PA0: J2.C (VIA_PA0), J14.20; also elsewhere on the board
/IO/VIA_PA1: J2.D (VIA_PA1), J14.18; also elsewhere on the board
/IO/VIA_PA2: J2.E (VIA_PA2), J14.16; also elsewhere on the board
/IO/VIA_PA3: J2.F (VIA_PA3), J14.14; also elsewhere on the board
/IO/VIA_PA4: J2.H (VIA_PA4), J14.12; also elsewhere on the board
/IO/VIA_PA5: J2.J (VIA_PA5), J14.10; also elsewhere on the board
/IO/VIA_PA6: J2.K (VIA_PA6), J14.8; also elsewhere on the board
/IO/VIA_PA7: J2.L (VIA_PA7), J14.6; also elsewhere on the board
/MAGIC/BHORIZ: J2.10 (HORIZ), J14.5; also elsewhere on the board
/MAGIC/BVERT: J2.9 (VERT), J14.7; also elsewhere on the board
/MAGIC/BVIDEO: J12.1, J14.21; also elsewhere on the board
/USER/VIDEO_OR_5V: J2.2 (~VIDEO), J12.2
GND: C76.2, J2.1 (GND), J2.12 (GND), J2.A (GND), J2.N (GND), J14.1; also elsewhere on the board

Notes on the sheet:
The VIDEO_OR_5V jumper allows partial compatibility with VIC-20 and C64 user port peripherals by delivering +5V on PIN_2 instead of PET video. (Example: TexElec SNES adapter)
USER PORT

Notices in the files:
test/system/ieee/hardware4040_test.cpp:
SPDX-License-Identifier: CC0-1.0
hw/rev-b/mainboard/kicad/Audio.kicad_sch:
License: CC0 1.0 Universal (Public Domain Dedication)
